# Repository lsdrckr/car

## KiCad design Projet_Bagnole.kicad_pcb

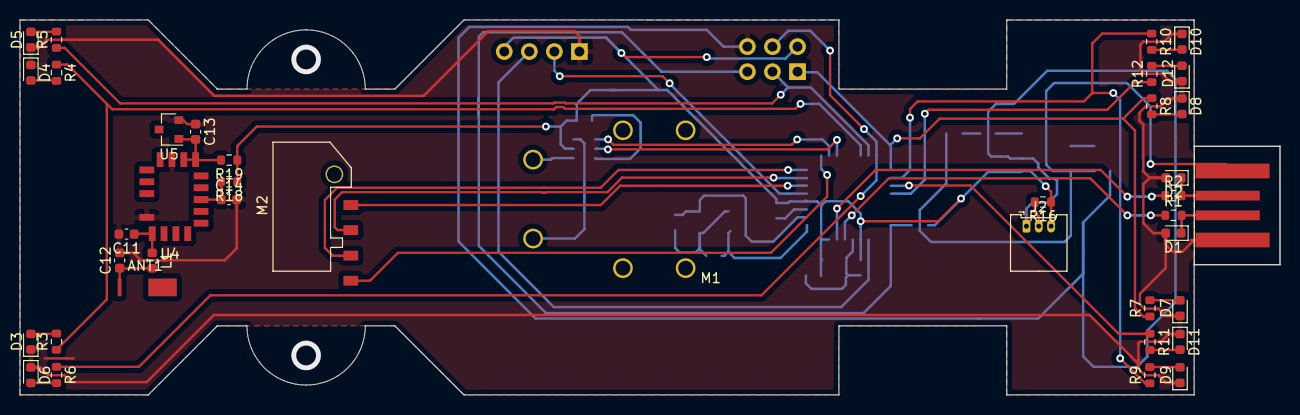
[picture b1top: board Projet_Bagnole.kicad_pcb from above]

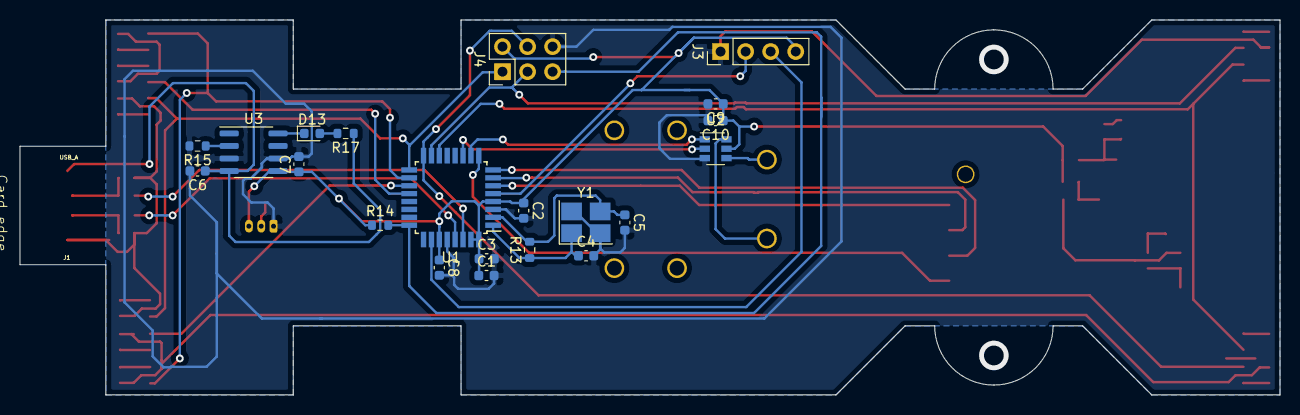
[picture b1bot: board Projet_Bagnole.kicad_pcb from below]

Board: 2 copper layers, 127.7 x 38.0 mm, 60 parts (21 on the bottom side), 45 nets.

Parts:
ANT1: ANT3216LL00R2400A
C1: 4.7uF; C_0603_1608Metric
C2, C3, C9: 100nF; C_0603_1608Metric
C4, C5: 22 pF; C_0603_1608Metric
C6: DNP; C_0603_1608Metric
C7, C10: 2.2uF; C_0603_1608Metric
C8, C11, C12: C; C_0603_1608Metric
C13, C14: 10uF; C_0603_1608Metric
D1, D2: D; D_0603_1608Metric
D3, D4, D5, D6, D7, D8, D9, D10, D11, D12, D13: LED; D_0603_1608Metric
J1: USB_A; USB-A-PCB
J2: Conn_01x03_Male; Molex_PicoBlade_53048-0310_1x03_P1.25mm_Horizontal
J3: Conn_01x04_Male; PinHeader_1x04_P2.54mm_Vertical
J4: AVR-ISP-6; PinHeader_2x03_P2.54mm_Vertical
L1: L; L_0603_1608Metric
M1: Motor_DC
M2: Stepper_Motor_bipolar; micro-slider
R1, R2: 220; R_0603_1608Metric
R3, R4, R5, R6, R7, R8, R9, R10, R11, R12: 330; R_0603_1608Metric
R13: 1M; R_0603_1608Metric
R14, R15: 10k; R_0603_1608Metric
R16, R19: R; R_0603_1608Metric
R17: 1k; R_0603_1608Metric
R18: 4.7k; R_0603_1608Metric
U1: ATmega16U2-AU; TQFP-32_7x7mm_P0.8mm
U2: DRV8210DRL; SOT-23-6
U3: MAX1811; SOIC-8_3.9x4.9mm_P1.27mm
U4: BM71BLE01FC2
U5: LM4040DBZ-2.5; SOT-23
Y1: Crystal_GND24; Crystal_SMD_SeikoEpson_FA238-4Pin_3.2x2.5mm_HandSoldering

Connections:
2.5V: C13.2, R19.2, U4.10, U4.11, U5.1
ANTENNE: C11.1, L1.1, U4.1
CHG: D13.1, U3.8
D+: R1.1, U1.29
D-: R2.1, U1.30
GND: C1.2, C2.2, C3.2, C4.2, C5.2, C6.2, C7.2, C8.2, C9.2, C10.2, C11.2, C12.2, C13.1, C14.2, D1.2, D2.2, D3.1, D4.1, D5.1, D6.1, D7.1, D8.1, D9.1, D10.1, D11.1, D12.1, J1.4, J2.1, J3.1, J4.6, R15.2, U1.3, U1.28, U2.3, U3.3, U3.6, U4.12, U4.17, U5.2, Y1.2, Y1.4
LED1: R3.1, R4.1, U1.14
LED2: J4.3, R5.1, U1.15
LED3: J4.4, R6.1, U1.16
LED4: J4.1, R7.1, R8.1, U1.17
LED5: R9.1, R10.1, U1.18
LED6: R11.1, U1.19
LED7: R12.1, U1.20
M1: M2.1, U1.6
M2: M2.2, U1.7
M3: M2.3, U1.8
M4: M2.4, U1.9
unnamed: ANT1.1, C12.1, L1.2
unnamed: C4.1, R13.1, U1.1, Y1.1
unnamed: C5.1, R13.2, U1.2, Y1.3
unnamed: D1.1, J1.3, R1.2
unnamed: D2.1, J1.2, R2.2
unnamed: D3.2, R3.2
unnamed: D4.2, R4.2
unnamed: D5.2, R5.2
unnamed: D6.2, R6.2
unnamed: D7.2, R7.2
unnamed: D8.2, R8.2
unnamed: D9.2, R9.2
unnamed: D10.2, R10.2
unnamed: D11.2, R11.2
unnamed: D12.2, R12.2
unnamed: D13.2, R17.2
unnamed: M1.1, U2.6
unnamed: M1.2, U2.4
PWM1: U1.10, U2.1
PWM2: U1.11, U2.2
RESET: J4.5, R14.2, U1.24
RST_N: C14.1, R18.2, U4.7
RX: J3.2, U1.5
SELI: R15.1, U3.2
TEMP: J2.2, R16.2
TX: J3.3, U1.26
VBUS: C6.1, J1.1, R17.1, U3.4
VCC: C1.1, C2.1, C3.1, C7.1, C8.1, C9.1, C10.1, J2.3, J3.4, J4.2, R14.1, R16.1, R18.1, R19.1, U1.4, U1.27, U1.31, U1.32, U2.5, U3.5

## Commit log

2023-02-28 first
2023-04-04 04/04 -Routage presque terminé
2023-04-07 Routage terminé (manque support roue)
2023-04-11 Test minuteur/pwm
2023-05-09 Fin des LEDs
2023-05-23 fonctionnement moteur
2023-05-23 Moteur fonctionnel
2023-05-23 The End Bientôt un transformers
